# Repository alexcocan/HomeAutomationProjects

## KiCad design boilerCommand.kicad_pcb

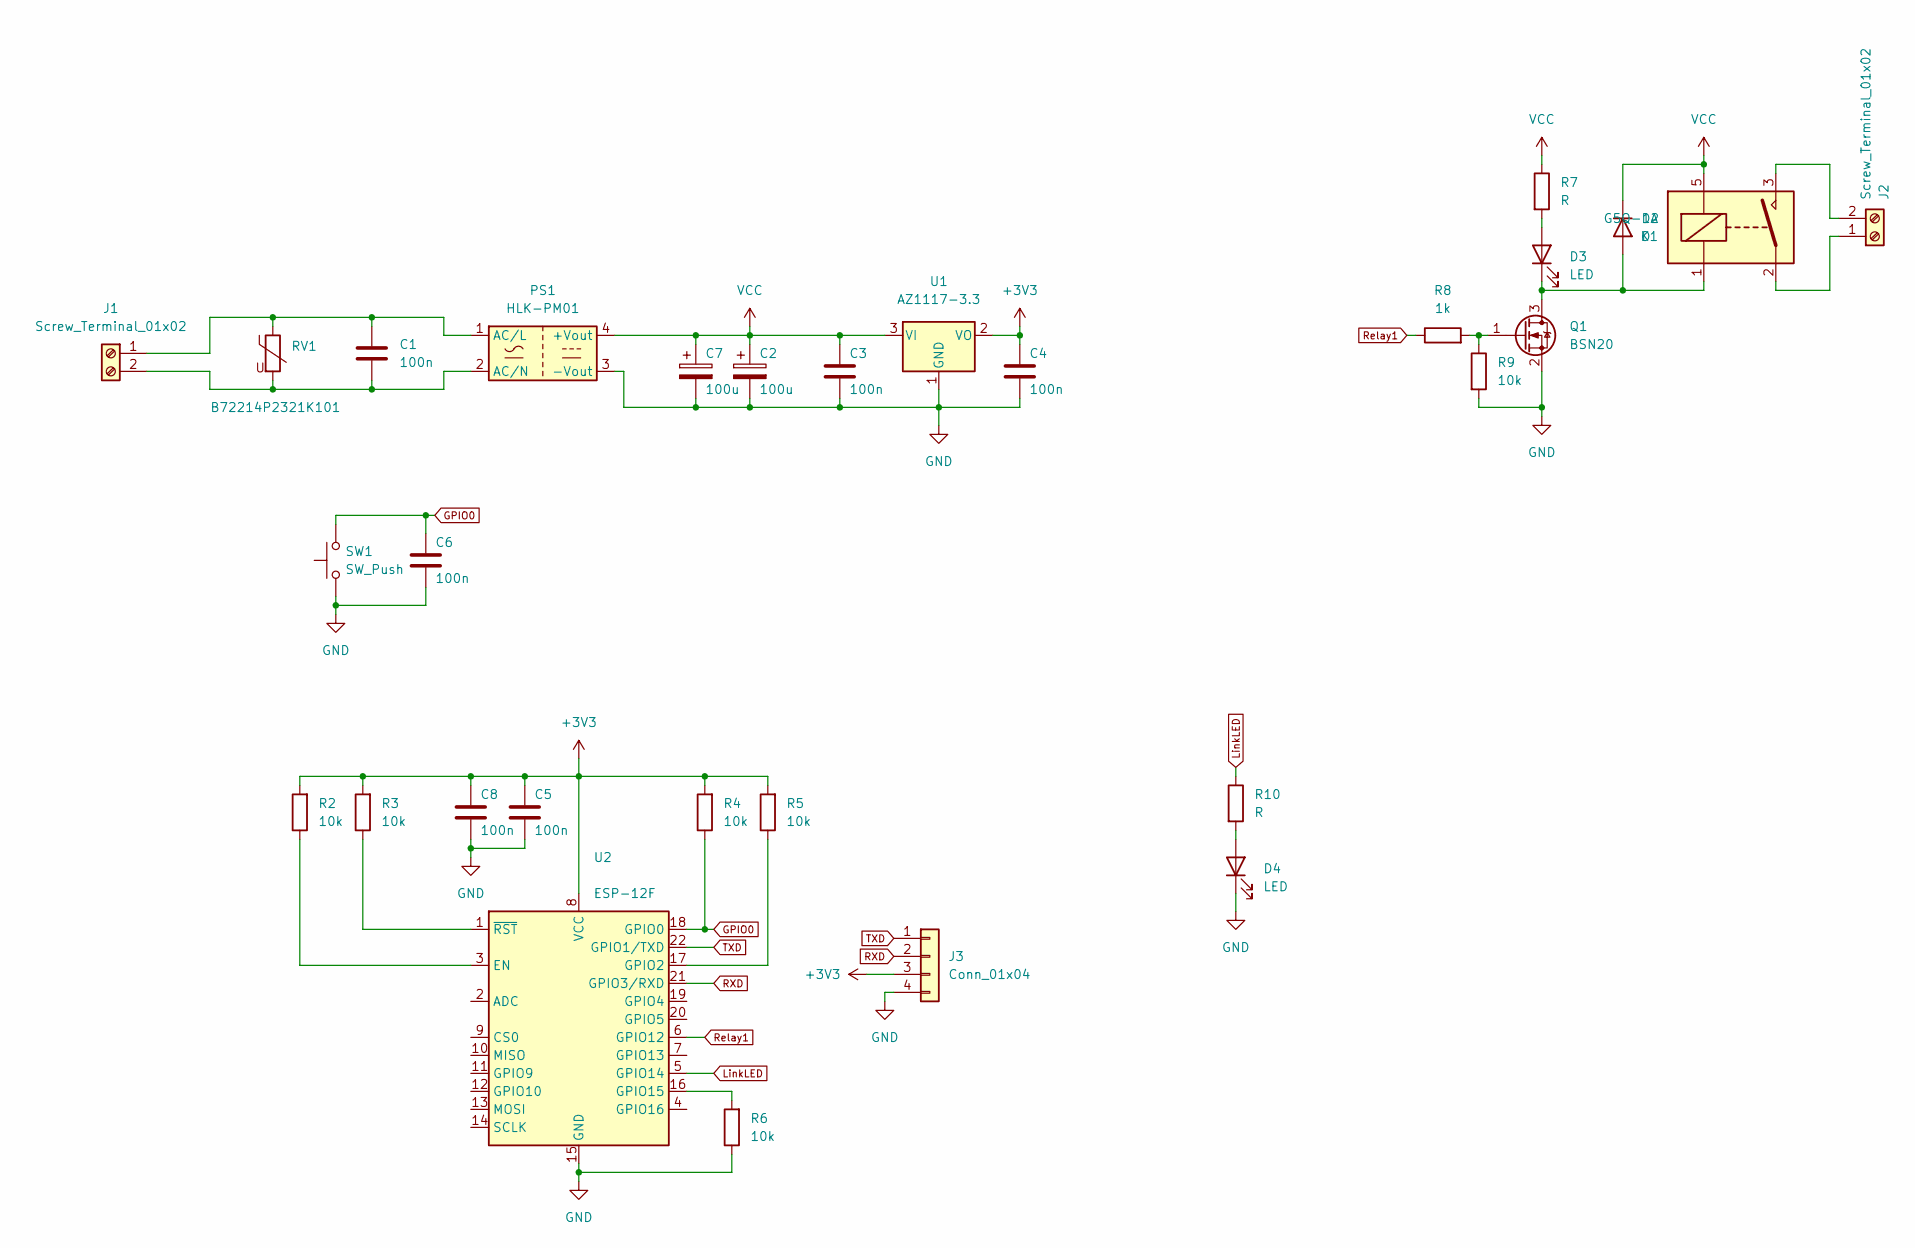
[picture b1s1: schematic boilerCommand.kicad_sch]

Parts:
C1: 100n; C_Rect_L11.5mm_W6.6mm_P10.00mm_MKT
C2, C7: 100u; CP_EIA-7343-31_Kemet-D
C3, C4, C5, C6, C8: 100n; C_0805_2012Metric_Pad1.18x1.45mm_HandSolder
D2: D; D_SMA
D3, D4: LED; LED_PLCC-2
J1, J2: Screw_Terminal_01x02; TerminalBlock_Phoenix_MKDS-1,5-2_1x02_P5.00mm_Horizontal
J3: Conn_01x04; JST_XH_B4B-XH-A_1x04_P2.50mm_Vertical
K1: G5Q-1A; Relay_SPST_Omron-G5Q-1A
PS1: HLK-PM01; Converter_ACDC_HiLink_HLK-PMxx
Q1: BSN20; SOT-23
R2, R3, R4, R5, R6, R9: 10k; R_0805_2012Metric_Pad1.20x1.40mm_HandSolder
R7, R10: R; R_0805_2012Metric_Pad1.20x1.40mm_HandSolder
R8: 1k; R_0805_2012Metric_Pad1.20x1.40mm_HandSolder
RV1: B72214P2321K101; RV_Disc_D16.5mm_W6.7mm_P7.5mm
SW1: SW_Push; SW_SPST_EVQP2
U1: AZ1117-3.3; SOT-223-3_TabPin2
U2: ESP-12F; ESP-12E

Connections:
+3V3: C4.1, C5.1, C8.1, J3.3, R2.2, R3.2, R4.2, R5.2, U1.2 (VO), U2.8 (VCC)
GND: C2.2, C3.2, C4.2, C5.2, C6.2, C7.2, C8.2, D4.1 (K), J3.4, PS1.3 (-Vout), Q1.2 (S), R6.1, R9.2, SW1.1, U1.1 (GND), U2.15 (GND)
GPIO0: C6.1, R4.1, SW1.2, U2.18 (GPIO0)
LinkLED: R10.1, U2.5 (GPIO14)
unnamed: C1.1, J1.1, PS1.1 (AC/L), RV1.1
unnamed: C1.2, J1.2, PS1.2 (AC/N), RV1.2
unnamed: D2.2 (A), D3.1 (K), K1.1, Q1.3 (D)
unnamed: D3.2 (A), R7.2
unnamed: D4.2 (A), R10.2
unnamed: J2.1, K1.2
unnamed: J2.2, K1.3
unnamed: Q1.1 (G), R8.2, R9.1
unnamed: R2.1, U2.3 (EN)
unnamed: R3.1, U2.1 (~RST)
unnamed: R5.1, U2.17 (GPIO2)
unnamed: R6.2, U2.16 (GPIO15)
RXD: J3.2, U2.21 (GPIO3/RXD)
Relay1: R8.1, U2.6 (GPIO12)
TXD: J3.1, U2.22 (GPIO1/TXD)
VCC: C2.1, C3.1, C7.1, D2.1 (K), K1.5, PS1.4 (+Vout), R7.1, U1.3 (VI)

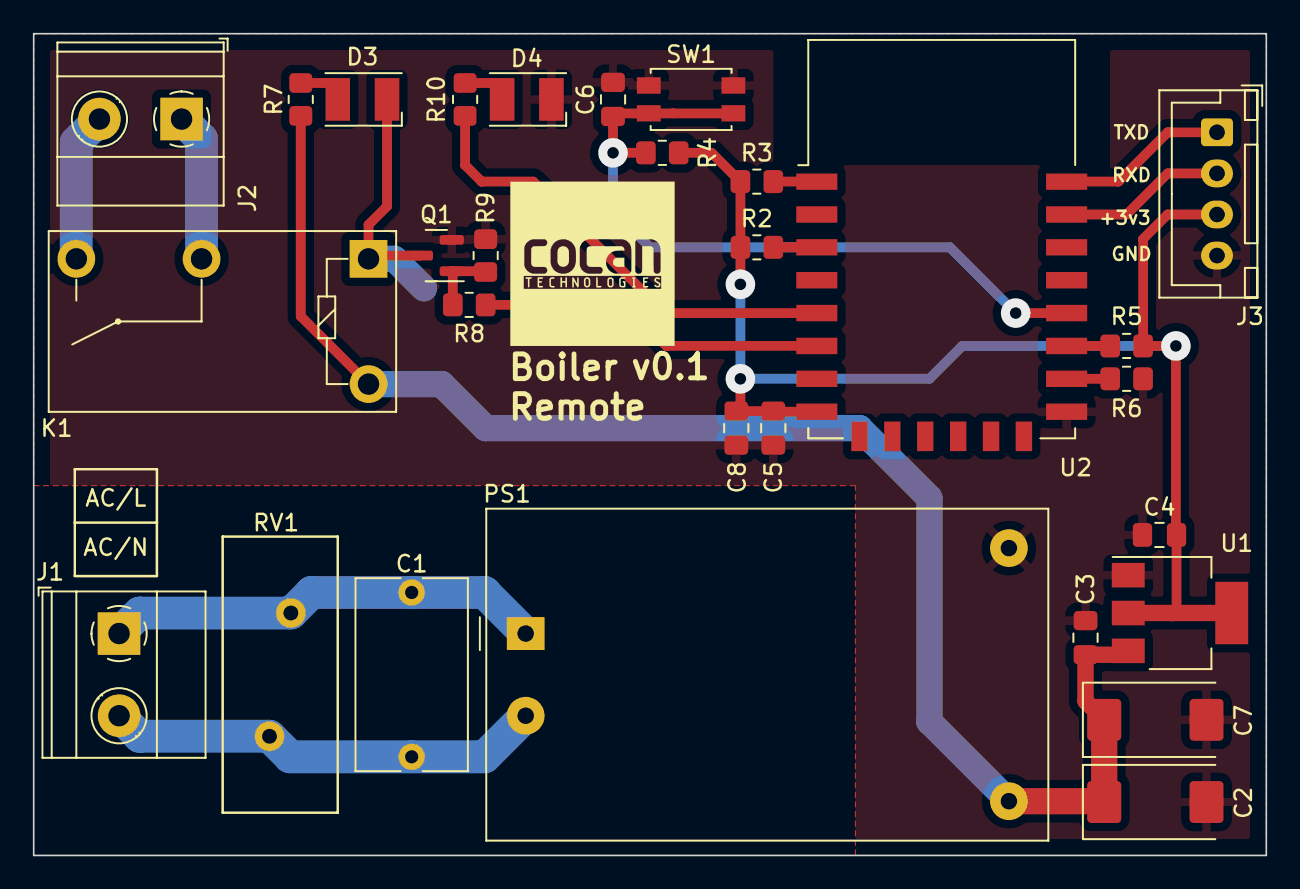
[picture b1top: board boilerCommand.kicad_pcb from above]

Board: 2 copper layers, 75.0 x 50.0 mm, 30 parts (1 on the bottom side), 20 nets.
